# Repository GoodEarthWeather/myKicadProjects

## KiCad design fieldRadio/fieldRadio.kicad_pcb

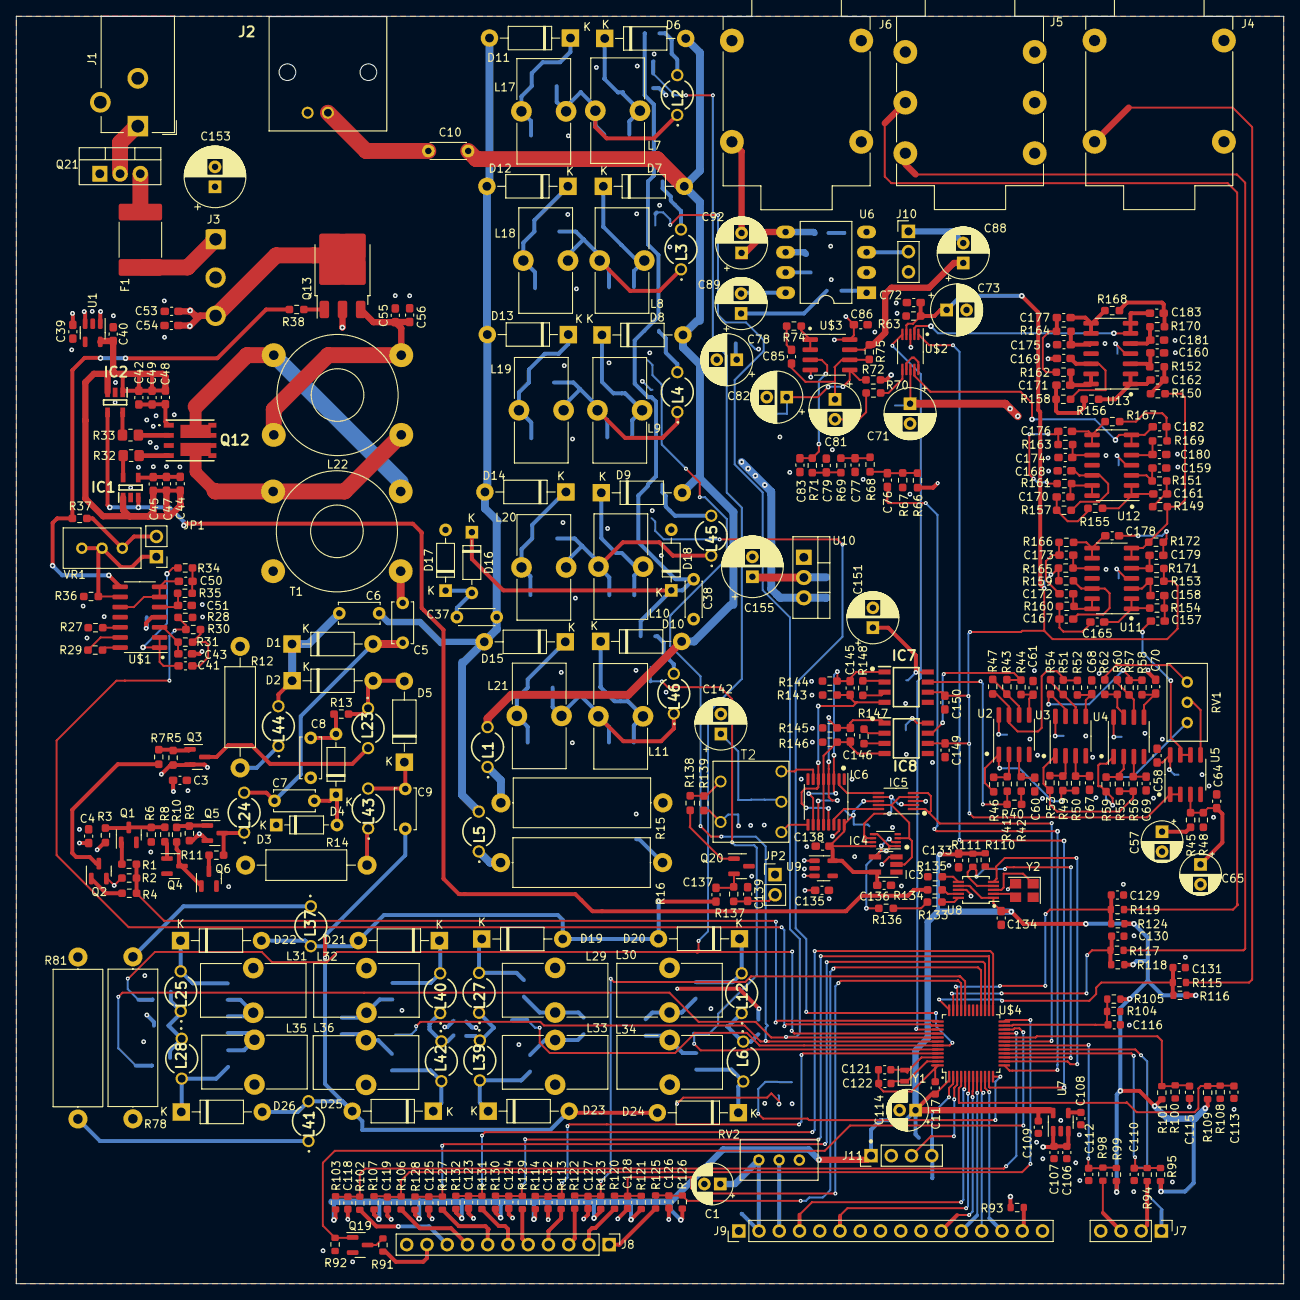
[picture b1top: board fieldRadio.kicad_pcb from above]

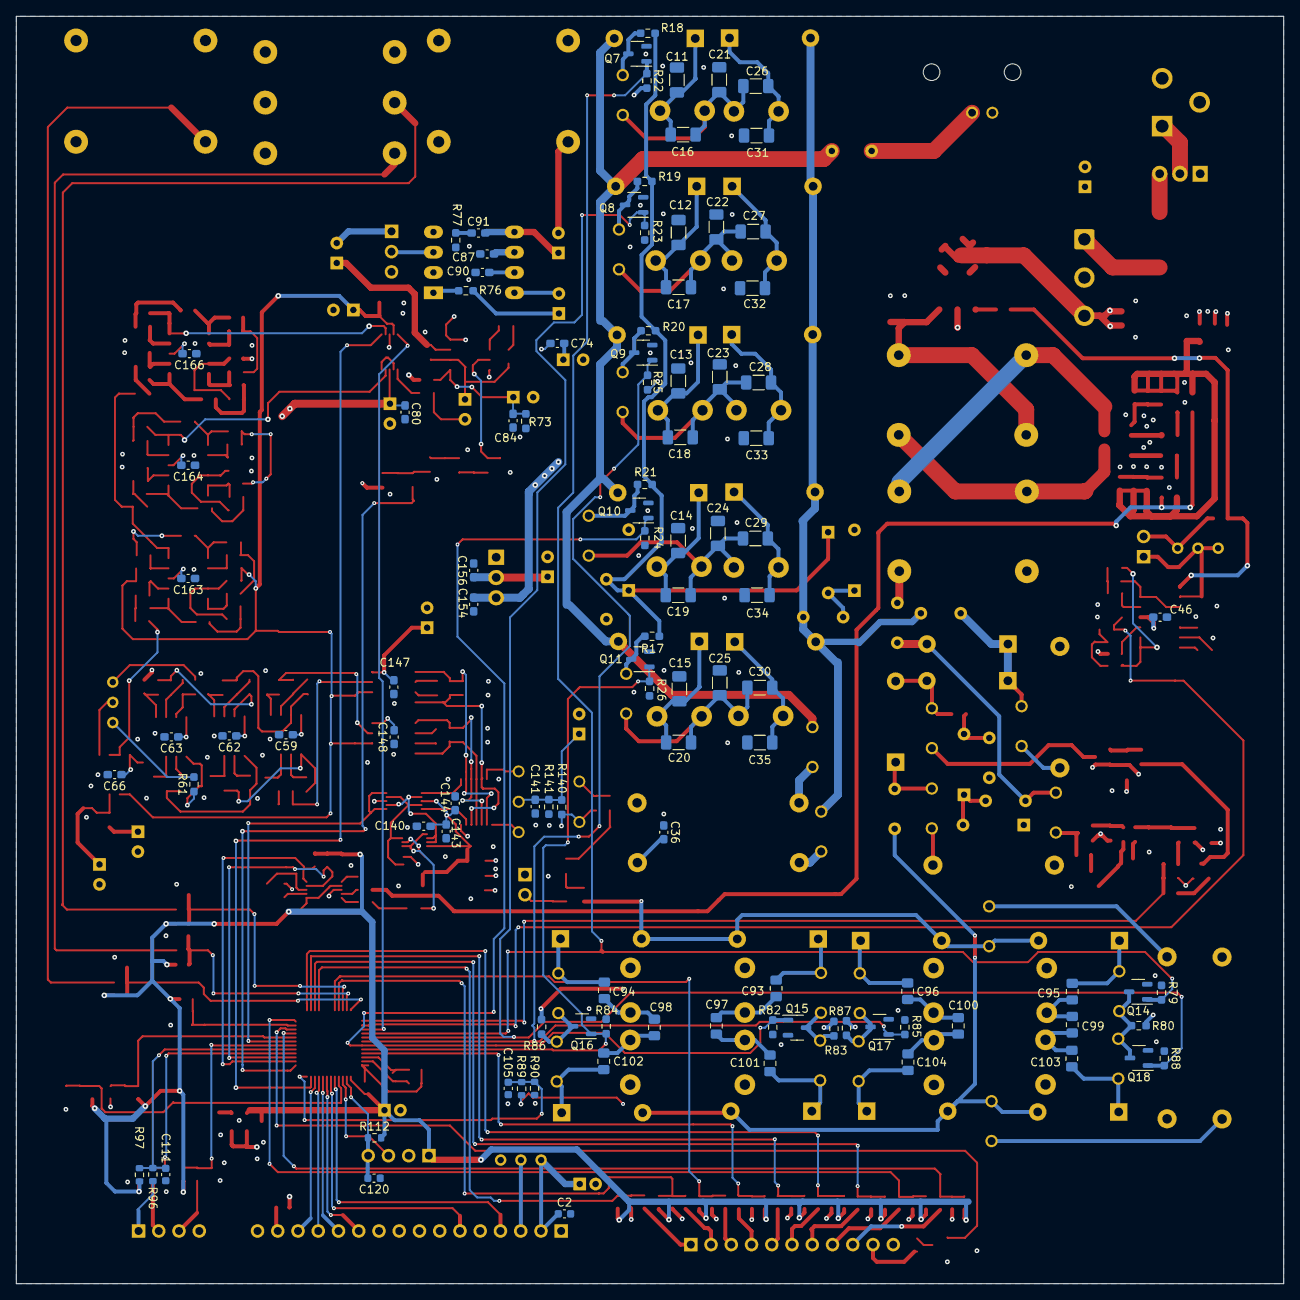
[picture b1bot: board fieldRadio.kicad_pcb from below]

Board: 4 copper layers, 159.0 x 159.0 mm, 481 parts (104 on the bottom side), 275 nets.

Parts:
C1, C114: 10uF; CP_Radial_D5.0mm_P2.00mm
C2, C105, C107, C109, C110, C111, C112, C113, C115, C116, C117, C118, C119, C123, C124, C125, C126, C127, C128, C129, C130, C131, C132: 0.1uF; C_0603_1608Metric
C3, C39, C45, C47, C48, C49, C55, C56, C135, C138, C144, C165: 1uF; C_0603_1608Metric_Pad1.08x0.95mm_HandSolder
C4, C36, C42, C44, C46, C54, C58, C59, C62, C63, C64, C66, C72, C74, C76, C77, C79, C80, C83, C84, C86, C136, C139, C140, C141, C143, C147, C148, C149, C150, C154, C156, C163, C164, C166, C183: 0.1uF; C_0603_1608Metric_Pad1.08x0.95mm_HandSolder
C5, C6, C8, C9: 0.1uF; C_Disc_D5.0mm_W2.5mm_P5.00mm
C7: 15pF; C_Disc_D5.0mm_W2.5mm_P5.00mm
C10: 0.1uF; C_Disc_D4.3mm_W1.9mm_P5.00mm
C11: 628p; C_1206_3216Metric_Pad1.33x1.80mm_HandSolder
C12: 435p; C_1206_3216Metric_Pad1.33x1.80mm_HandSolder
C13: 314p; C_1206_3216Metric_Pad1.33x1.80mm_HandSolder
C14: 244p; C_1206_3216Metric_Pad1.33x1.80mm_HandSolder
C15: 209p; C_1206_3216Metric_Pad1.33x1.80mm_HandSolder
C16: 89p; C_1206_3216Metric_Pad1.33x1.80mm_HandSolder
C17: 62p; C_1206_3216Metric_Pad1.33x1.80mm_HandSolder
C18: 44p; C_1206_3216Metric_Pad1.33x1.80mm_HandSolder
C19: 35p; C_1206_3216Metric_Pad1.33x1.80mm_HandSolder
C20: 30p; C_1206_3216Metric_Pad1.33x1.80mm_HandSolder
C21: 1218p; C_1206_3216Metric_Pad1.33x1.80mm_HandSolder
C22: 844p; C_1206_3216Metric_Pad1.33x1.80mm_HandSolder
C23: 609p; C_1206_3216Metric_Pad1.33x1.80mm_HandSolder
C24: 474p; C_1206_3216Metric_Pad1.33x1.80mm_HandSolder
C25: 406p; C_1206_3216Metric_Pad1.33x1.80mm_HandSolder
C26: 202p; C_1206_3216Metric_Pad1.33x1.80mm_HandSolder
C27: 140p; C_1206_3216Metric_Pad1.33x1.80mm_HandSolder
C28: 101p; C_1206_3216Metric_Pad1.33x1.80mm_HandSolder
C29: 79p; C_1206_3216Metric_Pad1.33x1.80mm_HandSolder
C30: 67p; C_1206_3216Metric_Pad1.33x1.80mm_HandSolder
C31: 557p; C_1206_3216Metric_Pad1.33x1.80mm_HandSolder
C32: 386p; C_1206_3216Metric_Pad1.33x1.80mm_HandSolder
C33: 279p; C_1206_3216Metric_Pad1.33x1.80mm_HandSolder
C34: 217p; C_1206_3216Metric_Pad1.33x1.80mm_HandSolder
C35: 186p; C_1206_3216Metric_Pad1.33x1.80mm_HandSolder
C37: 15pF; C_Disc_D4.3mm_W1.9mm_P5.00mm
C38: 470pF; C_Disc_D4.3mm_W1.9mm_P5.00mm
C40: 2.2uF; C_0603_1608Metric_Pad1.08x0.95mm_HandSolder
C41, C50: 710-885012206073; C_0603_1608Metric_Pad1.08x0.95mm_HandSolder
C43: 710-885012206071; C_0603_1608Metric_Pad1.08x0.95mm_HandSolder
C51: 80-C0603C223K3R; C_0603_1608Metric_Pad1.08x0.95mm_HandSolder
C53, C137: 0.01uF; C_0603_1608Metric_Pad1.08x0.95mm_HandSolder
C57, C65: 4.7uF; CP_Radial_D5.0mm_P2.50mm
C60, C61, C67, C68, C69, C70: 0.01u; C_0603_1608Metric_Pad1.08x0.95mm_HandSolder
C71, C78: CAP_POLPTH1; CP_Radial_D6.3mm_P2.50mm
C73, C82: 4.7uF; CP_Radial_D6.3mm_P2.50mm
C81: 47uF; CP_Radial_D6.3mm_P2.50mm
C85, C87: 4.7uF; C_0603_1608Metric_Pad1.08x0.95mm_HandSolder
C88, C92: 100uF; CP_Radial_D6.3mm_P2.50mm
C89: DNS; CP_Radial_D6.3mm_P2.50mm
C90: DNS; C_0603_1608Metric_Pad1.08x0.95mm_HandSolder
C91: 47nF; C_0603_1608Metric_Pad1.08x0.95mm_HandSolder
C93, C101: 163pF; C_0805_2012Metric_Pad1.18x1.45mm_HandSolder
C94, C102: 136pF; C_0805_2012Metric_Pad1.18x1.45mm_HandSolder
C95, C103: 407pF; C_0805_2012Metric_Pad1.18x1.45mm_HandSolder
C96, C104: 204pF; C_0805_2012Metric_Pad1.18x1.45mm_HandSolder
C97: 95pF; C_0805_2012Metric_Pad1.18x1.45mm_HandSolder
C98: 79pF; C_0805_2012Metric_Pad1.18x1.45mm_HandSolder
C99: 237pF; C_0805_2012Metric_Pad1.18x1.45mm_HandSolder
C100: 118pF; C_0805_2012Metric_Pad1.18x1.45mm_HandSolder
C106: 1uF; C_0603_1608Metric
C108: 470pF; C_0603_1608Metric
C120: 1nF; C_0603_1608Metric
C121, C122: 22pF; C_0603_1608Metric
C133, C134, C179: 0.22uF; C_0603_1608Metric_Pad1.08x0.95mm_HandSolder
C142, C151: 10uF; CP_Radial_D6.3mm_P2.50mm
C145, C146: 330pF; C_0603_1608Metric_Pad1.08x0.95mm_HandSolder
C153, C155: 47uF; CP_Radial_D7.5mm_P2.50mm
C157: 0.82uF; C_0603_1608Metric_Pad1.08x0.95mm_HandSolder
C158: 0.39uF; C_0603_1608Metric_Pad1.08x0.95mm_HandSolder
C159, C168, C174, C177, C180: 0.012uF; C_0603_1608Metric_Pad1.08x0.95mm_HandSolder
C160, C169, C175, C181: 0.0033uF; C_0603_1608Metric_Pad1.08x0.95mm_HandSolder
C161: 0.015uF; C_0603_1608Metric_Pad1.08x0.95mm_HandSolder
C162: 0.0039uF; C_0603_1608Metric_Pad1.08x0.95mm_HandSolder
C167, C178: 0.47uF; C_0603_1608Metric_Pad1.08x0.95mm_HandSolder
C170: 0.018uF; C_0603_1608Metric_Pad1.08x0.95mm_HandSolder
C171: 0.0056uF; C_0603_1608Metric_Pad1.08x0.95mm_HandSolder
C172: 1.5uF; C_0603_1608Metric_Pad1.08x0.95mm_HandSolder
C173: 0.68uF; C_0603_1608Metric_Pad1.08x0.95mm_HandSolder
C176: 0.039uF; C_0603_1608Metric_Pad1.08x0.95mm_HandSolder
C182: 0.33uF; C_0603_1608Metric_Pad1.08x0.95mm_HandSolder
D1, D2, D5, D6, D7, D8, D9, D10, D11, D12, D13, D14, D15, D19, D20, D21, D22, D23, D24, D25, D26: 1N4007; D_DO-41_SOD81_P10.16mm_Horizontal
D3, D4, D16, D17, D18: 1N914; D_DO-35_SOD27_P7.62mm_Horizontal
F1: Polyfuse; Fuse_2920_7451Metric_Pad2.10x5.45mm_HandSolder
IC1, IC2: UCC27517DBVR; SOT95P280X145-5N
IC3: SN74LVC1G04DBVT; SOT-23-5_HandSoldering
IC4: SN74AUP2G79DCUR; VSSOP-8_2.3x2mm_P0.5mm
IC5: TS5A23157; VSSOP-10_3x3mm_P0.5mm
IC6: SN74CBTLV3253; TSSOP-16_4.4x5mm_P0.65mm
IC7, IC8: INA821ID; SOIC127P600X175-8N
J1: Barrel_Jack_Switch; BarrelJack_CUI_PJ-102AH_Horizontal
J2: 5227161-3; 52271613
J3: Conn_01x03; SolderWire-0.75sqmm_1x03_P4.8mm_D1.25mm_OD2.3mm
J4, J6: AudioJack2_Switch; Jack_6.35mm_Neutrik_NMJ4HFD3_Horizontal
J5: AudioJack3_Switch; Jack_6.35mm_Neutrik_NMJ6HFD2_Horizontal
J7, J11: Conn_01x04; PinHeader_1x04_P2.54mm_Vertical
J8: Conn_01x11; PinHeader_1x11_P2.54mm_Vertical
J9: Conn_01x16; PinHeader_1x16_P2.54mm_Vertical
J10: Conn_01x03; PinHeader_1x03_P2.54mm_Vertical
JP1, JP2: M02PTH; PinHeader_1x02_P2.54mm_Vertical
L1, L2, L3, L4, L5, L6, L12, L23, L24, L25, L27, L28, L37, L39, L40, L41, L42, L43, L44, L45, L46: B78148E1473J000; B78148E
L7: 728nH; L_Toroid_Vertical_L13.0mm_W6.5mm_P5.60mm
L8: 505nH; L_Toroid_Vertical_L13.0mm_W6.5mm_P5.60mm
L9: 364nH; L_Toroid_Vertical_L13.0mm_W6.5mm_P5.60mm
L10: 283nH; L_Toroid_Vertical_L13.0mm_W6.5mm_P5.60mm
L11: 243nH; L_Toroid_Vertical_L13.0mm_W6.5mm_P5.60mm
L17: 622nH; L_Toroid_Vertical_L13.0mm_W6.5mm_P5.60mm
L18: 431nH; L_Toroid_Vertical_L13.0mm_W6.5mm_P5.60mm
L19: 311nH; L_Toroid_Vertical_L13.0mm_W6.5mm_P5.60mm
L20: 242nH; L_Toroid_Vertical_L13.0mm_W6.5mm_P5.60mm
L21: 207nH; L_Toroid_Vertical_L13.0mm_W6.5mm_P5.60mm
L22: L_Ferrite_Coupled; Transformer_Toroid_Horizontal_D14.0mm_Amidon-T50
L29, L33: 341nH; L_Toroid_Vertical_L13.0mm_W6.5mm_P5.60mm
L30, L34: 284nH; L_Toroid_Vertical_L13.0mm_W6.5mm_P5.60mm
L31, L35: 852nH; L_Toroid_Vertical_L13.0mm_W6.5mm_P5.60mm
L32, L36: 426nH; L_Toroid_Vertical_L13.0mm_W6.5mm_P5.60mm
Q1, Q2, Q4: MMBT3904; SOT-23
Q3, Q5: PMV240SP; SOT-23
Q6: BSS123; SOT-23
Q7, Q8, Q9, Q10, Q11, Q14, Q15, Q16, Q17, Q18: BSS123; SOT-23-3
Q12: DMN10H220LPDW; DMN10H220LPDW13
Q13: NSS1C301ET4G; TO-252-3_TabPin4
Q19: MOSFET-NCHANNELBSS138; SOT-23
Q20: J309; SOT-23
Q21: IRF9540; TO-220-3_Vertical
R1, R4, R8, R61, R62, R139, R159: 1K; R_0603_1608Metric_Pad0.98x0.95mm_HandSolder
R2, R3, R5, R6, R9: 4.7K; R_0603_1608Metric_Pad0.98x0.95mm_HandSolder
R7, R10, R41, R43, R45, R46, R47, R48, R49, R51, R53, R54, R55, R57, R59, R60, R63, R68, R69, R71, R72, R73: 10K; R_0603_1608Metric_Pad0.98x0.95mm_HandSolder
R11, R27, R29, R37, R38, R133, R134, R135, R136: 0; R_0603_1608Metric_Pad0.98x0.95mm_HandSolder
R12, R14: 560; R_Axial_DIN0411_L9.9mm_D3.6mm_P15.24mm_Horizontal
R13, R17, R18, R19, R20, R21, R22, R23, R24, R25, R26, R79, R80, R82, R83, R84, R85, R86, R87, R88: 47K; R_0603_1608Metric_Pad0.98x0.95mm_HandSolder
R15, R16, R78, R81: 560; R_Axial_DIN0617_L17.0mm_D6.0mm_P20.32mm_Horizontal
R28, R30: 603-RC0603FR-0733KL; R_0603_1608Metric_Pad0.98x0.95mm_HandSolder
R31: 603-RC0603FR-078K2L; R_0603_1608Metric_Pad0.98x0.95mm_HandSolder
R32, R33: 603-RC0603FR-0733KL; R_0805_2012Metric_Pad1.20x1.40mm_HandSolder
R34: 603-RC0603FR-0736KL; R_0603_1608Metric_Pad0.98x0.95mm_HandSolder
R35: 603-RC0603FR-0711KL; R_0603_1608Metric_Pad0.98x0.95mm_HandSolder
R36: 603-RC0603FR-071KL; R_0603_1608Metric_Pad0.98x0.95mm_HandSolder
R40: 1.5K; R_0603_1608Metric_Pad0.98x0.95mm_HandSolder
R42: 200; R_0603_1608Metric_Pad0.98x0.95mm_HandSolder
R44: 5.23K; R_0603_1608Metric_Pad0.98x0.95mm_HandSolder
R50: 11.3K; R_0603_1608Metric_Pad0.98x0.95mm_HandSolder
R52, R151: 23.2K; R_0603_1608Metric_Pad0.98x0.95mm_HandSolder
R56: 51.1K; R_0603_1608Metric_Pad0.98x0.95mm_HandSolder
R58: 178K; R_0603_1608Metric_Pad0.98x0.95mm_HandSolder
R66, R67, R143, R144, R145, R146: 47k; R_0603_1608Metric_Pad0.98x0.95mm_HandSolder
R70: 270; R_0603_1608Metric_Pad0.98x0.95mm_HandSolder
R74, R155: 11K; R_0603_1608Metric_Pad0.98x0.95mm_HandSolder
R75: 10k; R_0603_1608Metric_Pad0.98x0.95mm_HandSolder
R76: DNS; R_0603_1608Metric_Pad0.98x0.95mm_HandSolder
R77: 10; R_0603_1608Metric_Pad0.98x0.95mm_HandSolder
R89: 9.09K; R_0603_1608Metric
R90, R95, R97, R99, R101, R103, R105, R107, R109, R114, R116, R118, R121, R123, R124, R126, R128, R130, R132: 1K; R_0603_1608Metric
R91: 220; R_0603_1608Metric
R92, R94, R96, R98, R100, R104, R108, R113, R115, R117, R119: 39K; R_0603_1608Metric
R93: 100; R_0603_1608Metric
R102, R106, R120, R122, R125, R127, R129, R131: 39k; R_0603_1608Metric
R110, R111: 2.7K; R_0603_1608Metric
R112: 47K; R_0603_1608Metric
R137, R138: 100; R_0603_1608Metric_Pad0.98x0.95mm_HandSolder
R140, R141, R170: 4.32K; R_0603_1608Metric_Pad0.98x0.95mm_HandSolder
R147, R148: 499; R_0603_1608Metric_Pad0.98x0.95mm_HandSolder
R149: 9.53K; R_0603_1608Metric_Pad0.98x0.95mm_HandSolder
R150: 10.5K; R_0603_1608Metric_Pad0.98x0.95mm_HandSolder
R152: 21K; R_0603_1608Metric_Pad0.98x0.95mm_HandSolder
R153, R165: 1.02K; R_0603_1608Metric_Pad0.98x0.95mm_HandSolder
R154: 866; R_0603_1608Metric_Pad0.98x0.95mm_HandSolder
R156: 8.06K; R_0603_1608Metric_Pad0.98x0.95mm_HandSolder
R157: 16.5K; R_0603_1608Metric_Pad0.98x0.95mm_HandSolder
R158: 18.7K; R_0603_1608Metric_Pad0.98x0.95mm_HandSolder
R160: 604; R_0603_1608Metric_Pad0.98x0.95mm_HandSolder
R161: 8.66K; R_0603_1608Metric_Pad0.98x0.95mm_HandSolder
R162: 6.04K; R_0603_1608Metric_Pad0.98x0.95mm_HandSolder
R163: 9.76K; R_0603_1608Metric_Pad0.98x0.95mm_HandSolder
R164: 11.8K; R_0603_1608Metric_Pad0.98x0.95mm_HandSolder
R166: 267; R_0603_1608Metric_Pad0.98x0.95mm_HandSolder
R167: 2.55K; R_0603_1608Metric_Pad0.98x0.95mm_HandSolder
R168: 1.96K; R_0603_1608Metric_Pad0.98x0.95mm_HandSolder
R169: 3.92K; R_0603_1608Metric_Pad0.98x0.95mm_HandSolder
R171: 9.09K; R_0603_1608Metric_Pad0.98x0.95mm_HandSolder
R172: 301; R_0603_1608Metric_Pad0.98x0.95mm_HandSolder
RV1: 1K; Potentiometer_Bourns_3296W_Vertical
RV2: R_Potentiometer; Potentiometer_Bourns_3386C_Horizontal
T1: 1:1; Transformer_Toroid_Horizontal_D14.0mm_Amidon-T50
T2: T50-TRIFILAR
U1: MIC5235-5.0YM5; SOT-23-5
U2, U3, U4, U5: OPA1678; SOIC-8_3.9x4.9mm_P1.27mm
U6: LM386; DIP-8_W10.16mm_LongPads
U7: MIC5219-3.3YM5; SOT-23-5
U8: Si5351A-B-GT; MSOP-10_3x3mm_P0.5mm
U9: MCP1802x-xx02xOT; SOT-23-5
U10: LM1085-5.0; TO-220-3_Vertical
U11, U12, U13: OPA1679; SOIC-14_3.9x8.7mm_P1.27mm
U$1: OPA1679IDR; SOIC-14_3.9x8.7mm_P1.27mm
U$2: TS5A23157; VSSOP-10_3x3mm_P0.5mm
U$3: OPA1678; SOIC-8_3.9x4.9mm_P1.27mm
U$4: MSP430FR2476TPT; LQFP-48_7x7mm_P0.5mm
VR1: 3296W-1-505LF; Potentiometer_Bourns_3296W_Vertical
Y1: 32.768kHz; Crystal_SMD_2012-2Pin_2.0x1.2mm
Y2: 25MHz; Crystal_SMD_Abracon_ABM8G-4Pin_3.2x2.5mm

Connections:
/15M: Q11.1 (G), Q16.1 (G), R26.2, R84.2, U$4.44 (P5.1/UCA0RXD/UCA0SOMI/TB0.3)
/17M: Q10.1 (G), Q15.1 (G), R24.2, R82.2, U$4.43 (P5.0/UCA0CLK/TB0.2)
/20M: Q9.1 (G), Q17.1 (G), R25.2, R85.2, U$4.42 (P4.7/UCA0STE/TB0.1)
/30M: Q8.1 (G), Q18.1 (G), R23.2, R88.2, U$4.41 (P6.2/TB0.0)
/40M: Q7.1 (G), Q14.1 (G), R22.2, R79.2, U$4.40 (P6.1/TB0CLK)
/Audio/SIDETONE: C76.2, U$4.13 (P1.1/UCB0CLK/TA0.1/COMP0.0/A1)
/Audio/audio_narrow: C182.2, U12.6 (-), U12.7, U$2.9 (NC1)
/Audio/audio_out: C92.2 (-), J6.T
/Audio/audio_wide: C183.2, U13.6 (-), U13.7, U$2.2 (NO1)
/Audio/filt_sel: U$2.1 (IN1), U$4.11 (P5.4/UCB1STE/TA3CLK/A11)
/Audio/mute: U$2.5 (IN2), U$4.39 (P3.6/UCB1SOMI/UCB1SCL)
/Audio/vbias: C72.1, C73.1 (+), C149.1, C150.2, IC7.6 (REF), IC8.6 (REF), R63.2, R153.1, R159.1, R165.1, R171.1, U5.1, U5.2 (-), U$2.4 (NO2)
/AudioFilters/HPLP Filters/in: C157.1, U5.6 (-), U5.7
/AudioFilters/I: IC7.7 (OUT), R40.1, R41.1
/AudioFilters/Q: IC8.7 (OUT), R43.1, R44.1
/BTN_BAND_SEL: J8.7, R127.1
/BTN_DIGIT_SEL: J8.6, R131.1
/BTN_FILTER_SEL: J8.5, R129.1
/BTN_MENU: J8.2, R120.1
/BTN_MODE: J8.4, R113.2
/BTN_MUTE: J8.8, R106.2
/BTN_SPOT: J8.1, R125.1
/BTN_TUNE: J8.3, R122.1
/BTN_TXMODE: J8.9, R102.2
/ENCODER_A: J7.1, R96.1
/ENCODER_B: J7.2, R94.1
/ENCODER_SW: J7.3, R98.1
/LCD_A: J9.15, R93.2
/LCD_DB4: J9.11, U$4.7 (P1.7/UCA0STE/SMCLK/TDO/A7)
/LCD_DB5: J9.12, U$4.8 (P4.3/UCB1SOMI/UCB1SCL/TB0.5/A8)
/LCD_DB6: J9.13, U$4.9 (P4.4/UCB1SIMO/UCB1SDA/TB0.6/A9)
/LCD_DB7: J9.14, U$4.10 (P5.3/UCB1CLK/TA3.0/A10)
/LCD_E: J9.6, U$4.6 (P1.6/UCA0CLK/TA1CLK/TDI/TCLK/A6)
/LCD_RS: J9.4, U$4.5 (P1.5/UCA0RXD/UCA0SOMI/TA1.1/TMS/A5)
/LCD_VO: J9.3, RV2.2
/LPF/HV: C38.1, D16.1 (K), D18.1 (K), R17.2, R18.2, R19.2, R20.2, R21.2
/LPF/antenna: C10.1, J2.C1
/LPF/trswitch: C6.2, C37.2, D11.2 (A), D12.2 (A), D13.2 (A), D14.2 (A), D15.2 (A), L5.2
/PADDLE_DAH: J5.T, R117.2
/PADDLE_DIT: J5.R, R119.2
/Preselector/input: C9.2, D23.2 (A), D24.2 (A), D25.2 (A), D26.2 (A), L41.2
/STRAIGHT_KEY: J4.T, R115.2
/TRSwitch/power_amp: C5.1, T1.3 (SA)
/TRSwitch/~T/R: R1.1, R2.2, R4.1, U$4.37 (P3.5/UCB1CLK/TB0TRG)
/TX_LED: J8.10, R91.2
/clock/CLK0: R133.2, R136.2
/clock/CLK1: IC1.3 (IN+), IC2.4 (IN-), R134.2
/clock/SCL: R111.2, U8.4 (SCL), U$4.15 (P1.3/UCB0SOMI/UCB0SCL/MCLK/A3)
/clock/SDA: R110.2, U8.5 (SDA), U$4.14 (P1.2/UCB0SIMO/UCB0SDA/TA0.2/A2/VEREF-)
/controller/CWTX_OUT: R28.1, R30.2, U$4.38 (P3.2/UCB1SIMO/UCB1SDA)
/controller/SIDEBAND_SEL: IC5.1 (IN1), IC5.5 (IN2), U$4.19 (P5.5/UCB0CLK/TA2CLK)
/powerAmp/VCC5.0: C40.2, C42.2, C44.2, C45.1, C47.1, C48.1, C49.1, IC1.1 (VDD), IC2.1 (VDD), IC2.3 (IN+), U1.5 (OUT)
/powerInput/PWR_IN: J1.1, Q21.2 (D)
/powerInput/PWR_SWTCH: F1.2, J3.1
/qsd/0-DEG: C145.2, IC6.6 (1B1), IC6.13 (2B4), IC7.4 (+IN), R143.2
/qsd/90-DEG: C146.1, IC6.5 (1B2), IC6.12 (2B3), IC8.4 (+IN), R146.2
/qsd/180-DEG: C145.1, IC6.3 (1B4), IC6.10 (2B1), IC7.1 (-IN), R144.2
/qsd/270-DEG: C146.2, IC6.4 (1B3), IC6.11 (2B2), IC8.1 (-IN), R145.2
/qsd/CLK0: IC4.1 (1CLK), IC4.5 (2CLK), R136.1
/qsd/ICLK: IC5.10 (COM1), IC6.14 (S0)
/qsd/P0: IC4.6 (2D), IC4.7 (1Q), IC5.2 (NO1), IC5.7 (NC2)
/qsd/P1: IC3.2 (A), IC4.3 (2Q), IC5.4 (NO2), IC5.9 (NC1)
/qsd/QCLK: IC5.6 (COM2), IC6.2 (S1)
/qsd/VCC3.3: C136.2, C138.2, C140.2, C143.1, C144.1, IC3.5 (VCC), IC4.8 (VCC), IC5.8 (V+), IC6.16 (VCC), U9.5 (VOUT)
/qsd/rf_in: C137.2, D19.2 (A), D20.2 (A), D21.2 (A), D22.2 (A), L37.2
GND: C1.2, C2.2, C3.2, C4.2, C8.1, C11.2, C12.2, C13.2, C14.2, C15.2, C21.2, C22.2, C23.2, C24.2, C25.2, C31.2, C32.2, C33.2, C34.2, C35.2, C36.1, C38.2, C39.1, C40.1, C42.1, C43.2, C44.1, C45.2, C46.1, C47.2, C48.2, C49.2, C51.2, C53.1, C54.1, C55.1, C56.1, C57.2, C58.2, C59.2, C60.2, C61.2, C62.2, C63.2, C64.2, C65.2, C66.2, C67.2, C68.2, C69.2, C70.2, C71.2 (-), C72.2, C73.2 (-), C74.1, C77.1, C78.2 (-), C79.1, C80.1, C82.2 (-), C83.1, C84.1, C86.1, C87.2, C90.1, C105.2, C106.2, C107.2, C108.2, C109.2, C110.2, C111.2, C112.2, C113.2, C114.2, C115.2, C116.2, C117.1, C118.2, C119.2, C120.1, C121.1, C122.1, C123.2, C124.2, C125.2, C126.2, C127.2, C128.2, C129.2, C130.2, C131.2, C132.2, C133.2, C134.2, C135.1, C136.1, C138.1, C139.1, C140.1, C141.1, C142.2 (-), C143.2, C144.2, C147.1, C148.1, C149.2, C150.1, C151.2 (-), C153.2, C154.2, C155.2, C156.2, C159.2, C160.2, C163.1, C164.1, C166.1, C168.2, C169.2, C174.2, C175.2, C180.2, C181.2, D3.1 (K), D17.2 (A), IC1.2 (GND), IC1.4 (IN-), IC2.2 (GND), IC3.3 (GND), IC4.4 (GND), IC5.3 (GND), IC6.1 (1~OE), IC6.8 (GND), IC6.15 (2~OE), IC7.5 (-VS), IC8.5 (-VS), J1.2, J1.3, J2.G1 (GND), J3.2, J4.S, J5.S, J6.S, J7.4, J8.11, J9.1, J9.5, J9.16, J10.3, J11.2, JP2.1, L29.2, L30.2, L31.2, L32.2, L33.2, L34.2, L35.2, L36.2, Q1.2 (E), Q2.2 (E), Q4.2 (E), Q6.2 (S), Q7.2 (S), Q8.2 (S), Q9.2 (S), Q10.2 (S), Q11.2 (S), Q12.1 (S), Q12.3 (S), Q14.2 (S), Q15.2 (S), Q16.2 (S), Q17.2 (S), Q18.2 (S), Q19.2 (S), Q20.3 (G), Q21.1 (G), R2.1, R6.1, R12.2, R14.2, R22.1, R23.1, R24.1, R25.1, R26.1, R27.1, R28.2, R36.2, R48.1, R63.1, R67.1, R73.2, R77.2, R79.1, R82.1, R84.1, R85.1, R88.1, R90.2, R92.1, R141.1, R143.1, R144.1, R145.1, R146.1, RV2.3, T1.4 (SB), U1.2 (GND), U2.4 (V-), U3.4 (V-), U4.4 (V-), U5.4 (V-), U6.2 (-), U6.4 (GND), U7.2 (GND), U8.8 (GND), U9.2 (GND), U10.1 (GND), U11.11 (V-), U12.11 (V-), U13.11 (V-), U$1.11 (V-), U$2.3 (GND), U$3.4 (V-), U$4.48 (DVSS), Y2.2, Y2.4
unnamed: C16.1, C21.1, C26.2, L2.1, L7.1, L17.2
unnamed: C17.1, C22.1, C27.2, L3.1, L8.1, L18.2
unnamed: C18.1, C23.1, C28.2, L4.1, L9.1, L19.2
unnamed: C19.1, C24.1, C29.2, L10.1, L20.2, L45.1
unnamed: C20.1, C25.1, C30.2, L11.1, L21.2, L46.1
unnamed: C41.1, R30.1, R31.2
unnamed: C50.1, R34.1, R35.2
unnamed: C76.1, R66.1, R67.2, R68.1
unnamed: C77.2, R68.2, R69.1
unnamed: C79.2, R69.2, R71.1
unnamed: C81.1 (+), C85.2, R75.1, U$3.6 (-IN)
unnamed: C81.2 (-), R70.2
unnamed: C82.1 (+), C84.2, R72.2, R73.1, U$3.5 (+IN)
unnamed: C85.1, R74.2
unnamed: C88.1 (+), R75.2, U$3.7 (OUT)
unnamed: C88.2 (-), J10.1
unnamed: C89.1 (+), R76.2
unnamed: C89.2 (-), U6.8 (GAIN)
unnamed: C91.1, R77.1
unnamed: C91.2, C92.1 (+), U6.5
unnamed: C93.1, C97.2, L29.1
unnamed: C94.1, C98.2, L30.1
unnamed: C95.1, C99.2, L31.1
unnamed: C100.1, C104.2, L36.1
unnamed: C96.1, C100.2, L32.1
unnamed: C97.1, C101.2, L33.1
unnamed: C98.1, C102.2, L34.1
unnamed: C99.1, C103.2, L35.1
unnamed: C139.2, JP2.2, R137.1
unnamed: C141.2, C142.1 (+), R140.1, R141.2, T2.4
unnamed: C157.2, C158.1, R154.1
unnamed: C161.1, R149.2, R151.1
unnamed: C162.1, R150.2, R152.1
unnamed: C165.2, C167.1, R160.1
unnamed: C170.1, R155.2, R157.1
unnamed: C171.1, R156.2, R158.1
unnamed: C172.2, C173.1, R166.1
unnamed: C176.1, R161.2, R163.1
unnamed: C177.1, R162.2, R164.1
unnamed: C178.2, C179.1, R172.1
unnamed: C182.1, R167.2, R169.1
unnamed: C183.1, R168.2, R170.1
unnamed: C5.2, C7.1, D1.2 (A), L24.2
unnamed: C6.1, D1.1 (K), D2.1 (K), L44.2
unnamed: D2.2 (A), D5.2 (A), L23.1, R13.2
unnamed: C7.2, D3.2 (A), D4.1 (K)
unnamed: C8.2, D4.2 (A), R13.1
unnamed: C9.1, D5.1 (K), L43.2
unnamed: C11.1, C16.2, D6.1 (K), L7.2
unnamed: C12.1, C17.2, D7.1 (K), L8.2
unnamed: C13.1, C18.2, D8.1 (K), L9.2
unnamed: C14.1, C19.2, D9.1 (K), L10.2
unnamed: C10.2, D6.2 (A), D7.2 (A), D8.2 (A), D9.2 (A), D10.2 (A), L1.2
unnamed: C15.1, C20.2, D10.1 (K), L11.2
unnamed: C26.1, C31.1, D11.1 (K), L17.1
unnamed: C27.1, C32.1, D12.1 (K), L18.1
unnamed: C28.1, C33.1, D13.1 (K), L19.1
unnamed: C29.1, C34.1, D14.1 (K), L20.1
unnamed: C30.1, C35.1, D15.1 (K), L21.1
unnamed: C37.1, D16.2 (A), D17.1 (K)
unnamed: C93.2, D19.1 (K), L27.2
unnamed: C94.2, D20.1 (K), L12.2
unnamed: C96.2, D21.1 (K), L40.2
unnamed: C95.2, D22.1 (K), L25.2
unnamed: C101.1, D23.1 (K), L39.2
unnamed: C102.1, D24.1 (K), L6.2
unnamed: C104.1, D25.1 (K), L42.2
unnamed: C103.1, D26.1 (K), L28.2
unnamed: IC1.5 (OUT), R32.1
unnamed: IC2.5 (OUT), R33.1
unnamed: IC3.4 (Y), IC4.2 (1D)
unnamed: IC6.7 (1A), T2.3
unnamed: IC6.9 (2A), T2.5
unnamed: IC7.2 (RG_1), R148.1
unnamed: IC7.3 (RG_2), R148.2
unnamed: IC8.2 (RG_1), R147.1
unnamed: IC8.3 (RG_2), R147.2
unnamed: J10.2, U6.3 (+)
unnamed: J11.3, U$4.3 (TEST/SBWTCK)
unnamed: C120.2, J11.4, R112.1, U$4.2 (RST/NMI/SBWTDIO)
unnamed: L1.1, R15.2
unnamed: L5.1, R16.2
unnamed: L37.1, R78.2
unnamed: L41.1, R81.2
unnamed: L43.1, R14.1
unnamed: L44.1, R12.1
unnamed: Q1.1 (B), R1.2
unnamed: Q1.3 (C), R3.1, R6.2, R8.1
unnamed: Q2.1 (B), R4.2
unnamed: Q2.3 (C), R7.1
unnamed: L23.2, Q3.3 (D)
unnamed: Q3.1 (G), R5.2, R7.2
unnamed: Q4.1 (B), R8.2
unnamed: Q4.3 (C), Q6.1 (G), R10.1
unnamed: L24.1, Q5.3 (D), R11.2
unnamed: Q5.1 (G), R9.2, R10.2
unnamed: Q6.3 (D), R11.1
unnamed: L2.2, Q7.3 (D), R18.1
unnamed: L3.2, Q8.3 (D), R19.1
unnamed: L4.2, Q9.3 (D), R20.1
unnamed: L45.2, Q10.3 (D), R21.1
unnamed: L46.2, Q11.3 (D), R17.1
unnamed: Q12.2 (G), R33.2
unnamed: Q12.4 (G), R32.2
unnamed: Q13.1 (B), R38.1
unnamed: C55.2, C56.2, L22.1, L22.4, Q13.3 (E)
unnamed: L25.1, L28.1, Q14.3 (D), Q18.3 (D), R80.1
unnamed: L27.1, L39.1, Q15.3 (D), R83.1
unnamed: L6.1, L12.1, Q16.3 (D), R86.1
unnamed: L40.1, L42.1, Q17.3 (D), R87.1
unnamed: Q19.3 (D), R91.1
unnamed: Q19.1 (G), R92.2, U$4.22 (P6.0/TA2.2/COMP0.3)
unnamed: Q20.1 (D), R138.2
unnamed: C137.1, Q20.2 (S), R137.2
unnamed: F1.1, Q21.3 (S)
unnamed: R40.2, R42.1
unnamed: R46.2, R49.1, R50.1, U2.1
unnamed: R47.2, R51.1, R52.1, U2.7
unnamed: R53.2, R55.1, R56.1, U3.1
unnamed: R54.2, R57.1, R58.1, U3.7
unnamed: R59.2, R61.1, U4.1
unnamed: R60.2, R62.1, U4.7
unnamed: R61.2, RV1.1
unnamed: R62.2, RV1.3
unnamed: R76.1, U6.1 (GAIN)
unnamed: R138.1, R139.2, T2.1
unnamed: L22.2, Q12.7 (D), Q12.8 (D), T1.1 (AA)
unnamed: L22.3, Q12.5 (D), Q12.6 (D), T1.2 (AB)
unnamed: C60.1, R42.2, U2.3 (+)
unnamed: R41.2, R46.1, U2.2 (-)
unnamed: C61.1, R44.2, U2.5 (+)
unnamed: R43.2, R47.1, U2.6 (-)
unnamed: C67.1, R50.2, U3.3 (+)
unnamed: R49.2, R53.1, U3.2 (-)
unnamed: C68.1, R52.2, U3.5 (+)
unnamed: R51.2, R54.1, U3.6 (-)
unnamed: C69.1, R56.2, U4.3 (+)
unnamed: R55.2, R59.1, U4.2 (-)
unnamed: C70.1, R58.2, U4.5 (+)
unnamed: R57.2, R60.1, U4.6 (-)
unnamed: C64.1, C65.1, R45.2, R48.2, U5.3 (+)
unnamed: RV1.2, U5.5 (+)
unnamed: C90.2, U6.7 (BYPASS)
unnamed: C108.1, U7.4 (BP)
unnamed: R133.1, U8.10 (CLK0)
unnamed: R134.1, U8.9 (CLK1)
unnamed: R135.1, U8.6 (CLK2)
unnamed: U8.2 (XA), Y2.3
unnamed: U8.3 (XB), Y2.1
unnamed: C158.2, R153.2, U11.3 (+)
unnamed: C165.1, R154.2, U11.1, U11.2 (-)
unnamed: C179.2, R171.2, U11.5 (+)
unnamed: R149.1, R150.1, R172.2, U11.6 (-), U11.7
unnamed: C173.2, R165.2, U11.10 (+)
unnamed: C178.1, R166.2, U11.8, U11.9 (-)
unnamed: C167.2, R159.2, U11.12 (+)
unnamed: C172.1, R160.2, U11.13 (-), U11.14
unnamed: C159.1, R151.2, U12.3 (+)
unnamed: C161.2, R155.1, U12.1, U12.2 (-)
unnamed: C180.1, R169.2, U12.5 (+)
unnamed: C174.1, R163.2, U12.10 (+)
unnamed: C176.2, R167.1, U12.8, U12.9 (-)
unnamed: C168.1, R157.2, U12.12 (+)
unnamed: C170.2, R161.1, U12.13 (-), U12.14
unnamed: C160.1, R152.2, U13.3 (+)
unnamed: C162.2, R156.1, U13.1, U13.2 (-)
unnamed: C181.1, R170.2, U13.5 (+)
unnamed: C175.1, R164.2, U13.10 (+)
unnamed: C177.2, R168.1, U13.8, U13.9 (-)
unnamed: C169.1, R158.2, U13.12 (+)
unnamed: C171.2, R162.1, U13.13 (-), U13.14
unnamed: C43.1, R31.1, U$1.3 (+IN)
unnamed: C41.2, R34.2, U$1.1 (OUT), U$1.2 (-IN)
unnamed: C51.1, R35.1, U$1.5 (+IN)
unnamed: C50.2, U$1.6 (-IN), U$1.7 (OUT), U$1.10 (+IN)
unnamed: JP1.1, R36.1, U$1.9 (-IN), VR1.1 (CCW), VR1.2 (WIPER)
unnamed: R37.2, R38.2, U$1.8 (OUT)
unnamed: R27.2, U$1.12 (+IN)
unnamed: R29.2, U$1.13 (-IN)
unnamed: R29.1, U$1.14 (OUT)
unnamed: U$2.7 (NC2), U$2.10 (COM1)
unnamed: R70.1, U$2.6 (COM2)
unnamed: C83.2, R71.2, U$3.3 (+IN)
unnamed: R74.1, U$3.1 (OUT), U$3.2 (-IN)
unnamed: C105.1, R89.2, R90.1, U$4.12 (P1.0/UCB0STE/TA0CLK/A0/VEREF+)
unnamed: C113.1, R108.2, R109.1, U$4.4 (P1.4/UCA0TXD/UCA0SIMO/TA1.2/TCK/A4/VREF+)
unnamed: C121.2, U$4.46 (P2.0/XOUT), Y1.2
unnamed: C122.2, U$4.47 (P2.1/XIN), Y1.1
unnamed: C110.1, R94.2, R95.2, U$4.16 (P2.2/ACLK/COMP0.1)
unnamed: C123.1, R131.2, R132.1, U$4.25 (P2.3/TA2.0)
unnamed: C126.1, R125.2, R126.1, U$4.28 (P2.4/UCA1CLK)
unnamed: C131.1, R115.1, R116.2, U$4.36 (P2.7/UCB1STE)
unnamed: C116.1, R104.2, R105.1, U$4.23 (P3.0/TA2.2)
unnamed: C125.1, R127.2, R128.1, U$4.27 (P3.1/UCA1STE)
unnamed: C119.1, R106.1, R107.2, U$4.24 (P3.3/TA2.1)
unnamed: C124.1, R129.2, R130.1, U$4.26 (P3.4/TA2CLK/COMP0OUT)
unnamed: C127.1, R122.2, R123.1, U$4.32 (P3.7/TA3.2)
unnamed: C128.1, R120.2, R121.2, U$4.33 (P4.0/TA3.1)
unnamed: C129.1, R119.1, R124.2, U$4.34 (P4.1/TA3.0)
unnamed: C130.1, R117.1, R118.2, U$4.35 (P4.2/TA3CLK)
unnamed: C111.1, R96.2, R97.2, U$4.17 (P4.5/UCB0SOMI/UCB0SCL/TA3.2)
unnamed: C112.1, R98.2, R99.2, U$4.18 (P4.6/UCB0SIMO/UCB0SDA/TA3.1)
unnamed: C132.1, R113.1, R114.2, U$4.45 (P5.2/UCA0TXD/UCA0SIMO/TB0.4)
unnamed: C115.1, R100.2, R101.1, U$4.20 (P5.6/UCB0STE/TA2.0)
unnamed: C118.1, R102.1, R103.2, U$4.21 (P5.7/TA2.1/COMP0.2)
unnamed: JP1.2, R37.1, VR1.3 (CW)
VDD3.3: C109.1, C114.1, C117.2, C133.1, C134.1, J11.1, R95.1, R97.1, R99.1, R101.2, R103.1, R105.2, R107.1, R109.2, R110.1, R111.1, R112.2, R114.1, R116.1, R118.1, R121.1, R123.2, R124.1, R126.2, R128.2, R130.2, R132.2, U7.5 (OUT), U8.1 (VDD), U8.7 (VDDO), U$4.1 (DVCC)
VDD5: C1.1, C2.1, C57.1, C58.1, C59.1, C62.1, C63.1, C66.1, C71.1 (+), C80.2, C106.1, C107.1, C135.2, C147.2, C148.2, C151.1 (+), C155.1, C156.1, C163.2, C164.2, C166.2, IC7.8 (+VS), IC8.8 (+VS), J9.2, R45.1, R93.1, R139.1, R140.2, RV2.1, T2.2, U2.8 (V+), U3.8 (V+), U4.8 (V+), U5.8 (V+), U7.1 (IN), U7.3 (EN), U9.1 (VIN), U9.3 (~SHDN), U10.2 (VO), U11.4 (V+), U12.4 (V+), U13.4 (V+), U$2.8 (V+)
VDD12: C3.1, C4.1, C36.2, C39.2, C46.2, C53.2, C54.2, C74.2, C78.1 (+), C86.2, C87.1, C153.1, C154.1, D18.2 (A), J3.3, Q3.2 (S), Q5.2 (S), Q13.2 (C), Q13.4 (C), R3.2, R5.1, R9.1, R15.1, R16.1, R66.2, R72.1, R78.1, R80.2, R81.1, R83.2, R86.2, R87.2, R89.1, U1.1 (IN), U1.3 (EN), U6.6 (V+), U10.3 (VI), U$1.4 (V+), U$3.8 (V+)

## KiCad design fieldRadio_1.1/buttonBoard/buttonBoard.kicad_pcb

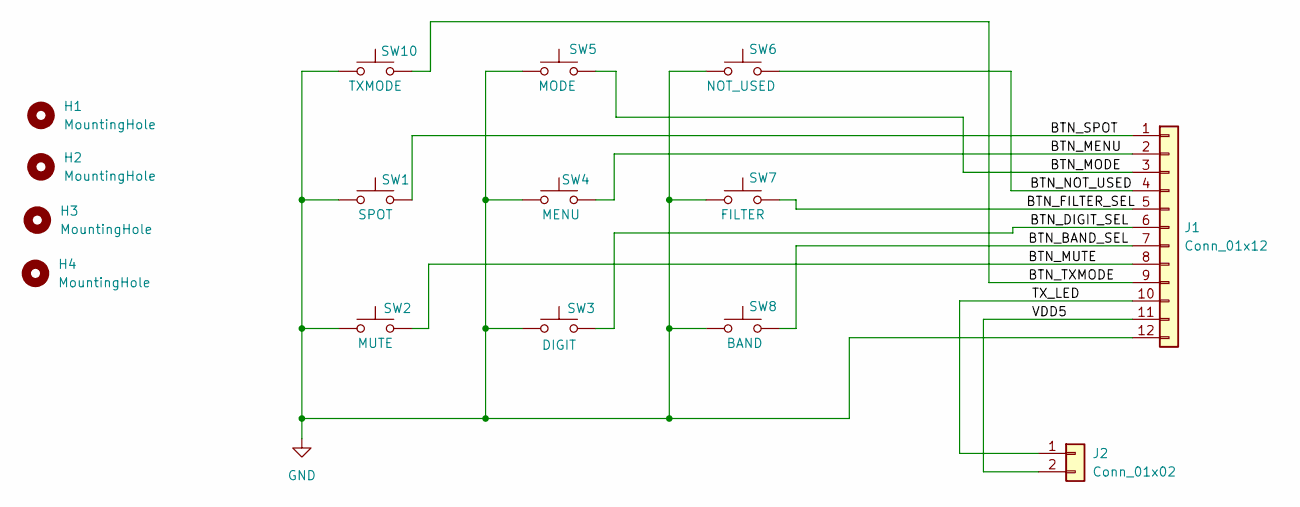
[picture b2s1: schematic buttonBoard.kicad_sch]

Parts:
H1, H2, H3, H4: MountingHole; MountingHole_3.2mm_M3
J1: Conn_01x12; PinHeader_1x12_P2.54mm_Horizontal
J2: Conn_01x02; PinHeader_1x02_P2.54mm_Horizontal
SW1: SPOT; SW_PUSH-12mm
SW2: MUTE; SW_PUSH-12mm
SW3: DIGIT; SW_PUSH-12mm
SW4: MENU; SW_PUSH-12mm
SW5: MODE; SW_PUSH-12mm
SW6: NOT_USED; SW_PUSH-12mm
SW7: FILTER; SW_PUSH-12mm
SW8: BAND; SW_PUSH-12mm
SW10: TXMODE; SW_PUSH-12mm

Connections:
/BTN_BAND_SEL: J1.7, SW8.2
/BTN_DIGIT_SEL: J1.6, SW3.2
/BTN_FILTER_SEL: J1.5, SW7.2
/BTN_MENU: J1.2, SW4.2
/BTN_MODE: J1.3, SW5.2
/BTN_MUTE: J1.8, SW2.2
/BTN_NOT_USED: J1.4, SW6.2
/BTN_SPOT: J1.1, SW1.2
/BTN_TXMODE: J1.9, SW10.2
/TX_LED: J1.10, J2.1
/VDD5: J1.11, J2.2
GND: J1.12, SW1.1, SW2.1, SW3.1, SW4.1, SW5.1, SW6.1, SW7.1, SW8.1, SW10.1

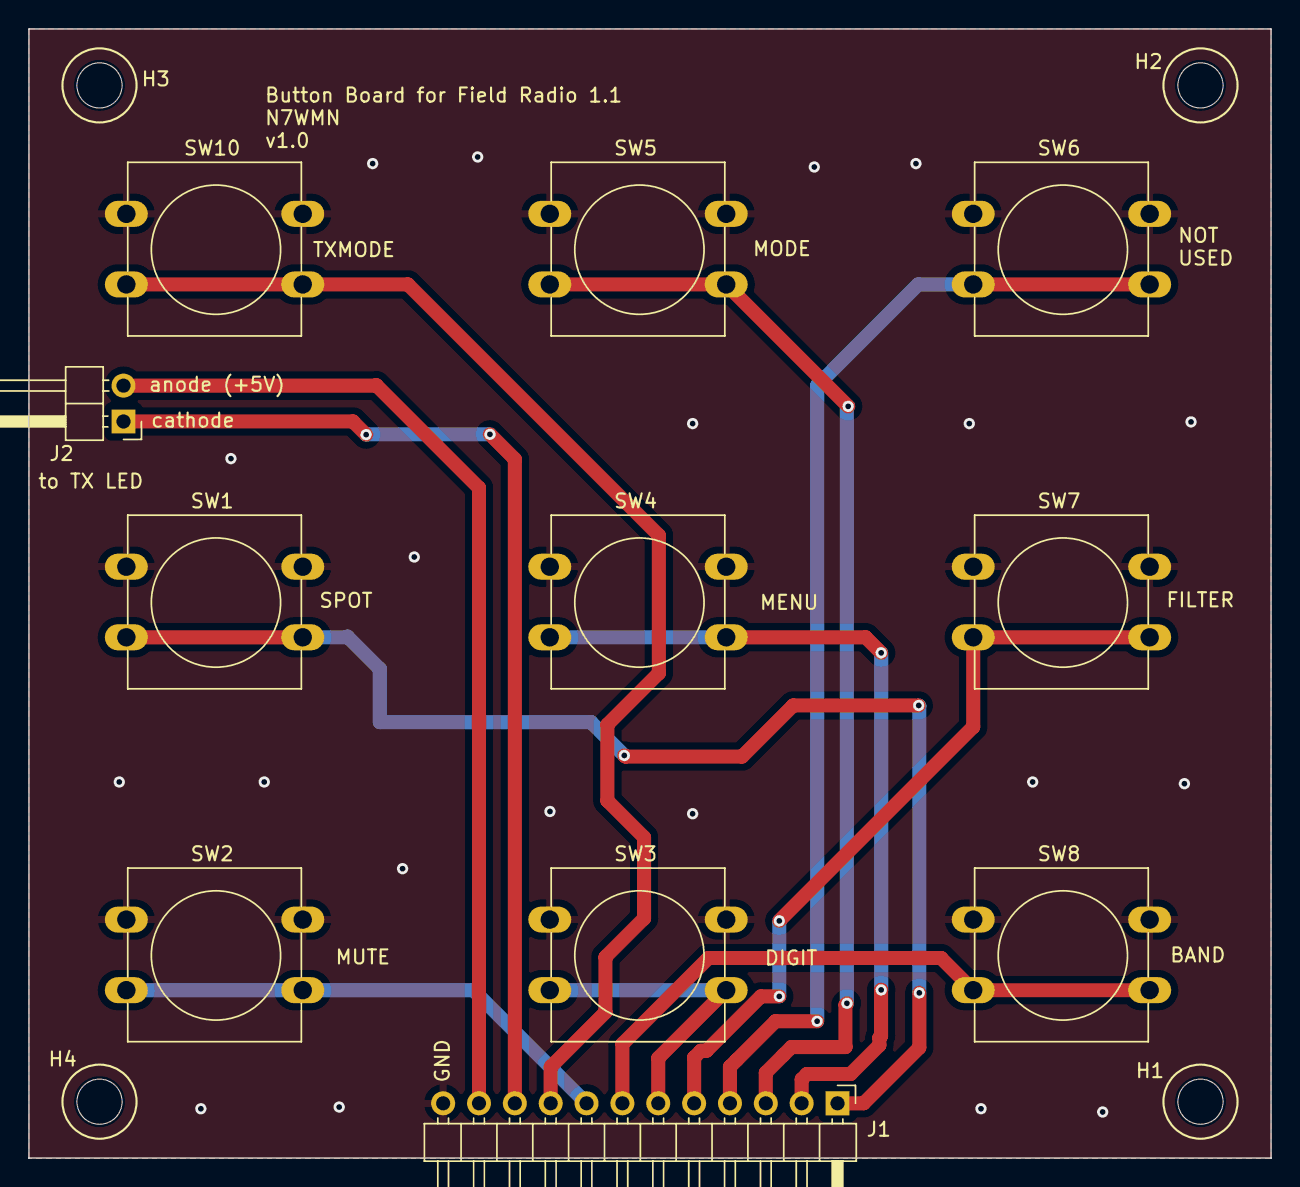
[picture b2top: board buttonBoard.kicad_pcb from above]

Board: 2 copper layers, 88.0 x 80.0 mm, 15 parts (0 on the bottom side), 12 nets.
